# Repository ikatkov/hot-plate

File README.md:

# Hot plate for PCB rework and reflow

# Notes

## General

The heating is not uniform (enough?). The father points of the hotplate are ~5C colder than the center, where the ceramic heating element is located. Typically, one would expect it to even out, but due to the high temperature of operation (150C-200C), fringes lose heat at a higher rate. 

A typical PCB is made of FR4 glass-reinforced epoxy resin laminate, turns out it's a decent insulator. As the result, the top side of the PCB is ~25C colder than the hotplate surface. Perhaps lots of plated vias would transfer the heat better. Add this 25C if running the plate on manual control. Adjust reflow profile accordingly.

If FR4 start to smoke - it's way too hot or too hot for way too long. If that has happened, the FR4 substrate has likely expanded already. So it might have ruined your impedance-controlled traces. 

Reflow should take less than 5min from the cold PCB to the end, all three phases - preheat, soak, reflow.

One good practice is to use the hot plate as preheating only, set it to ~150C and then use the hot air solder station to activate and melt the solder paste.

Temperature variation ±5C does not matter. You want to heat, solder, and cool down as fast as possible.

Max rate of heating for this particular hotplate element is about +2C/sec, still air colling is -1C/sec.

You can place some container/insulation over the hot plate to reduce the heat loss, but it only raises the temperature by about +5C. On the other hand, you can blow over the PCB and instantly lower the temperature by a few degrees.

## Hardware

The temperature probe must be placed right on the heater element or as close as possible. Any significant time delay between temperature control and measurement will destabilize the control loop. 
The wrong way is to put a thermocouple probe on the plate's far side. It introduces about 15seconds of dead time. 
The right way is to shove it into the ceramic heater.

Watch out for the metal case shorting signal lines to the ground. Everything on the low-voltage side of the PCB must be insulated from the metal enclosure.

The thermocouple wire can be cut to a convenient length.

## Software

MAX6675 has a resolution of 0.25C and an accuracy of ±2C. It takes approx ~200ms to take a reading, i.e., the fastest possible control loop cycle is 4Hz.

A solid-state relay can turn off at every 1/2 cycle of the AC sinus wave. The maximum delay for 60 Hz AC power is 1/2 cycle or 8.33 ms.
Every 266.67ms or 32 half AC cycles, the algo measures the temperature, does PID computations, and decides on the PWM duty cycle for the next control cycle.

PWM cycle is 266.67ms, which we split into 2^5 intervals. Therefore we have 2^5 control bits.
PID output variable will range from 0 to 32;
Timer2 is set for interrupts at a 120Hz rate (because half-cycles)

The Max rate of heating for this particular hotplate element is about +2C/sec below 180C and ~1C above, still air colling is approx +1C/sec. So Arduino PID library is modified to half differential coefficient to accommodate this.

I had fun fine-tuning PID coefficients to get a fast response and avoid overshoot, but this temperature fidelity does not mater. 

# Fabrication

Assemble all these pieces together
* Heating plate, [like this]("hot-plate.png")
* IEC 320-C14 Receptacle, Male Blades, panel mount, this is the socket at the back
* SPDT AC 250V switch, this is the main power switch
* metal case with lot's of slots
* 3d printed enclosure for display pcb, [picture](display-board-case.png) , [STEP file](display-case.step)
* two pcbs, see below
* M3 screews, washers, stand-outs, kapton tape, 14AWG wire for mains, thermocouple wire, IDC ribbon, silicon antiskid pads

## Safety

### Electrical
Bond ground wire from mains to the metal case, as soon as it enters the enclosure. Wire both hot and neutral through the SPDT switch to the pcb connectors. Observe neutral/hot polarity on the pcb. The hotplate aluminum is bonded via M3 screw via standout to the metal case.

The main pcb (power board) has a MOV and a 2A fuse. MCU is on isolated supply.

### Thermal 

Powerboard pcb has 85C thermal fuse to protect AC-DC convertor, wires and other electornic components. The temperature gradient below the hot plate is quite significant. When the hot plate is at +200C, the tallest point of the PCB, and thus the closest point to the hot measures +45C, with +20C ambient.

Arduino PID firmware limits (software) hotplate max temperature to +230C, the heating plate has +260C thermostat inside. Firmware also limits heating to 30min max.

## Power board 

### BOM
| Refs | Qty | Component | Description |
| ----- | --- | ---- | ----------- |
| BZ1 | 1 | Buzzer | Buzzer, polarized |
| C1 | 1 | 220uF | Polarized capacitor, US symbol |
| D1 | 1 | LED | Light emitting diode |
| F1 | 1 | Temp Fuse 85C | Fuse |
| F2 | 1 | Fuse 2A | Fuse |
| J1 | 1 | LINE/LOAD | Any wire to board connector |
| J2 | 1 | DISPLAY | IDC ribbon connector |
| J3 | 1 | PROG | Panel mount connector |
| K1 | 1 | G3MB-202P | https://www.mouser.com/datasheet/2/307/g3mb_0609-1189645.pdf |
| Q1 | 1 | 2N2222A | Any NPN transistor, collector/base/emitter |
| R1, R2, R3, R4 | 4 | 10k | Resistor |
| R5, R6 | 2 | 1k | Resistor |
| RV1 | 1 | 10D391K | https://www.mouser.com/datasheet/2/54/mov10d-777448.pdf |
| U1 | 1 | HLK-PM01 | https://datasheet.lcsc.com/szlcsc/1909111105_HI-LINK-HLK-PM24_C399250.pdf |
| U2 | 1 | Arduino | Any AVR MCU with 32Kb+ of flash, 2Kb+ of RAM |
| U3 | 1 | MAX6675 | https://datasheets.maximintegrated.com/en/ds/MAX6675.pdf |

## Display board 

### BOM

| Refs | Qty | Component | Description |
| ----- | --- | ---- | ----------- |
| J1 | 1 | TO_PWR_BOARD | IDC ribbon connector |
| J2 | 1 | OLED DISPLAY | 0.91" OLED LCD Display Module SSD1306 IIC 128x32|
| SW1,SW2,SW3,SW4 | 1 | BUTTON_X | Momentary switch, button should be tall enough to stick out from the case |

[STEP file]("display-case.step")
.

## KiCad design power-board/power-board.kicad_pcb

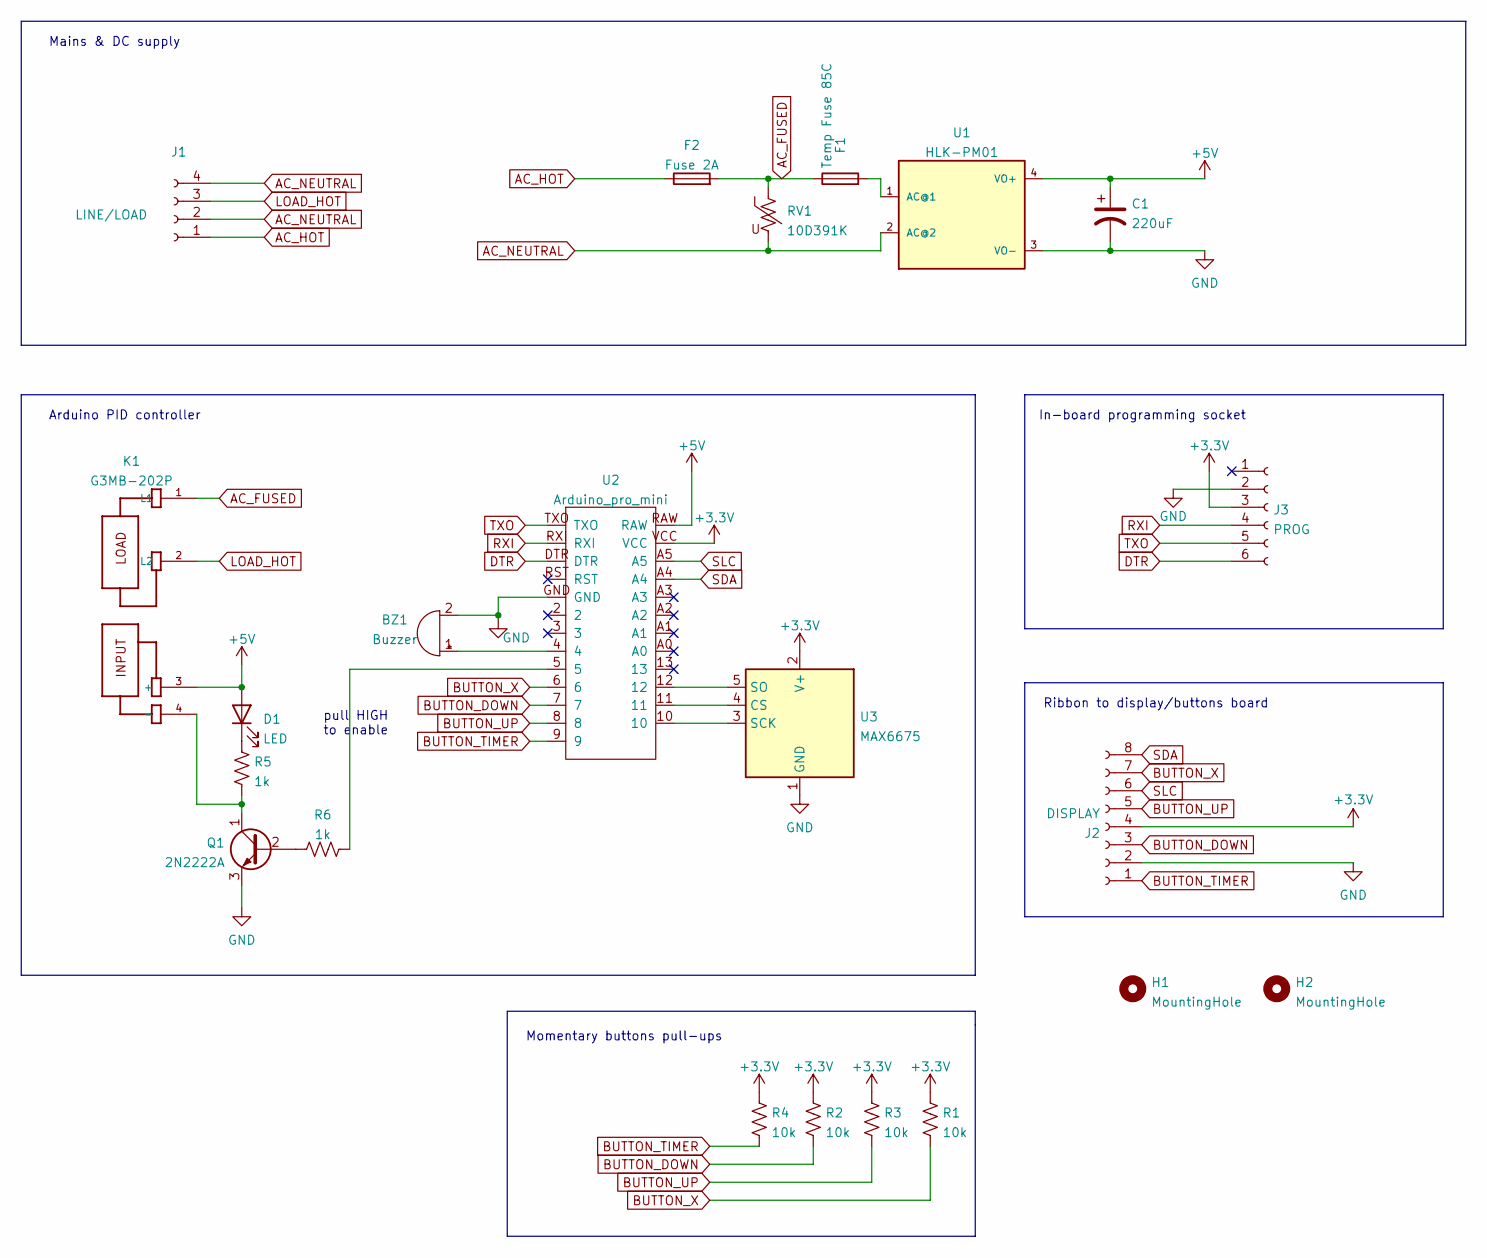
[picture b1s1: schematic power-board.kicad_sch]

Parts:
BZ1: Buzzer; Buzzer-GT-0905A
C1: 220uF; CP_Radial_D8.0mm_P5.00mm
D1: LED; LED_D5.0mm
F1: Temp Fuse 85C; R_Axial_DIN0414_L11.9mm_D4.5mm_P5.08mm_Vertical
F2: Fuse 2A; R_Axial_DIN0414_L11.9mm_D4.5mm_P5.08mm_Vertical
H1, H2: MountingHole; MountingHole_3.2mm_M3
J1: LINE/LOAD; WAGO_250-204_4_terminalblock
J2: DISPLAY; IDC-Header_2x04_P2.54mm_Vertical
J3: PROG; Connector_Mini-DIN_Female_6Pin_2rows
K1: G3MB-202P; RELAY_G3MB-202P
Q1: 2N2222A; TO-92L_Wide
R1, R2, R3, R4: 10k; R_Axial_DIN0204_L3.6mm_D1.6mm_P7.62mm_Horizontal
R5, R6: 1k; R_Axial_DIN0204_L3.6mm_D1.6mm_P7.62mm_Horizontal
RV1: 10D391K; RV_Disc_D12mm_W3.9mm_P7.5mm
U1: HLK-PM01
U2: Arduino_pro_mini; ARDUINO_PRO_MINI
U3: MAX6675; Thermocouple module

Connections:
+3V3: J2.4, J3.3, R1.1, R2.1, R3.1, R4.1, U2.VCC, U3.2 (V+)
+5V: C1.1, D1.2 (A), K1.3 (+), U1.4 (VO+), U2.RAW
AC_FUSED: F1.1, F2.2, K1.1 (L1), RV1.1
AC_HOT: F2.1, J1.1
AC_NEUTRAL: J1.2, J1.4, RV1.2, U1.2 (AC@2)
BUTTON_DOWN: J2.3, R2.2, U2.7
BUTTON_TIMER: J2.1, R4.2, U2.9
BUTTON_UP: J2.5, R3.2, U2.8
BUTTON_X: J2.7, R1.2, U2.6
DTR: J3.6, U2.DTR
GND: BZ1.2 (+), C1.2, J2.2, J3.2, Q1.3 (E), U1.3 (VO-), U2.GND, U3.1 (GND)
LOAD_HOT: J1.3, K1.2 (L2)
unnamed: BZ1.1 (-), U2.4
unnamed: D1.1 (K), R5.1
unnamed: F1.2, U1.1 (AC@1)
unnamed: K1.4 (-), Q1.1 (C), R5.2
unnamed: Q1.2 (B), R6.1
unnamed: R6.2, U2.5
unnamed: U2.10, U3.3 (SCK)
unnamed: U2.11, U3.4 (CS)
unnamed: U2.12, U3.5 (SO)
RXI: J3.4, U2.RXI
SDA: J2.8, U2.A4
SLC: J2.6, U2.A5
TXO: J3.5, U2.TXO

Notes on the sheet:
In-board programming socket
Ribbon to display/buttons board
Arduino PID controller
pull HIGH to enable
Momentary buttons pull-ups
Mains & DC supply

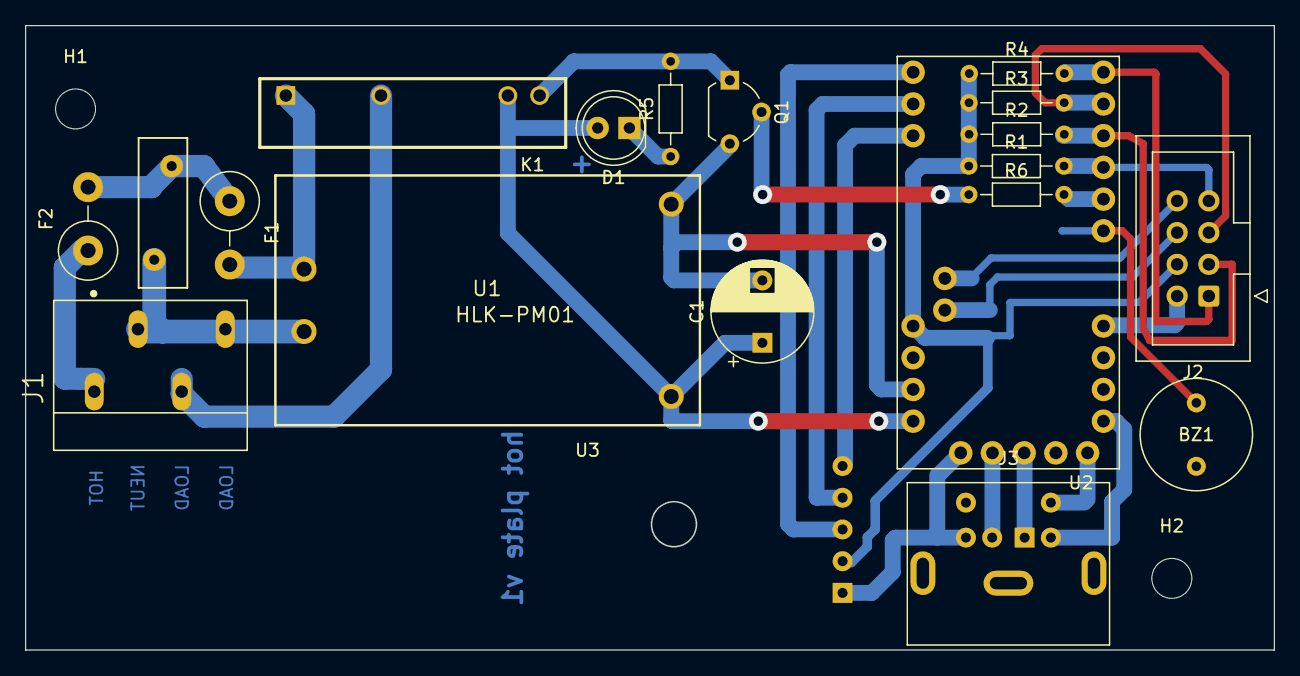
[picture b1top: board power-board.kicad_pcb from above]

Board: 2 copper layers, 100.0 x 50.0 mm, 22 parts (0 on the bottom side), 25 nets.

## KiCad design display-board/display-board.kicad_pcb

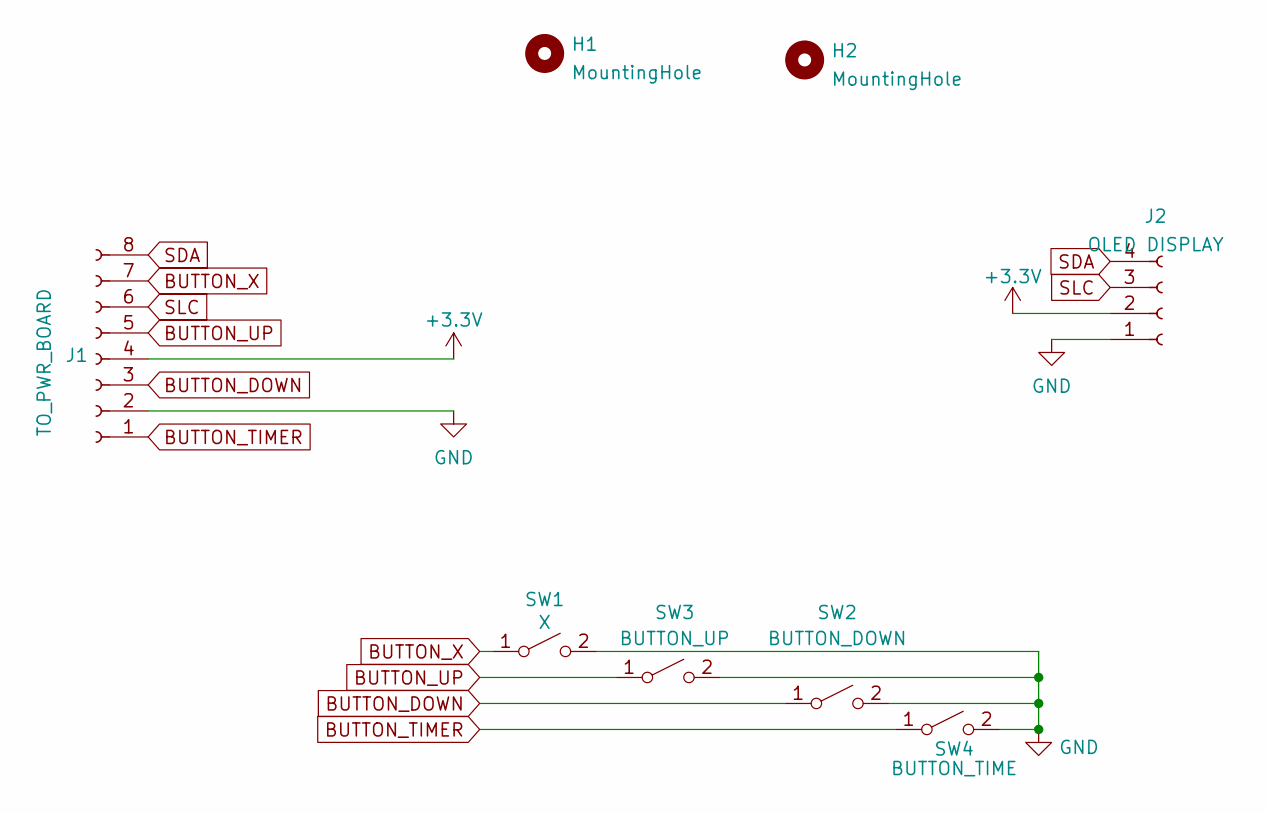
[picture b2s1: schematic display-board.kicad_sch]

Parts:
H1, H2: MountingHole; MountingHole_3.2mm_M3
J1: TO_PWR_BOARD; IDC-Header_2x04_P2.54mm_Vertical
J2: OLED DISPLAY; SSD1306-0.91-OLED-4pin-128x32
SW1: X; SW_PUSH_6mm_H4.3mm
SW2: BUTTON_DOWN; SW_PUSH_6mm_H4.3mm
SW3: BUTTON_UP; SW_PUSH_6mm_H4.3mm
SW4: BUTTON_TIME; SW_PUSH_6mm_H4.3mm

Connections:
+3V3: J1.4, J2.2
BUTTON_DOWN: J1.3, SW2.1 (A)
BUTTON_TIMER: J1.1, SW4.1 (A)
BUTTON_UP: J1.5, SW3.1 (A)
BUTTON_X: J1.7, SW1.1 (A)
GND: J1.2, J2.1, SW1.2 (B), SW2.2 (B), SW3.2 (B), SW4.2 (B)
SDA: J1.8, J2.4
SLC: J1.6, J2.3

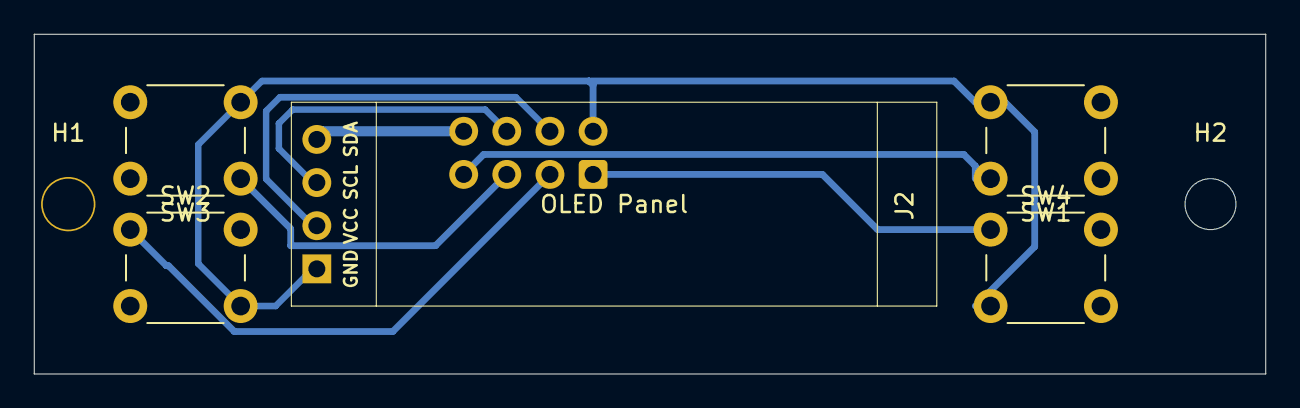
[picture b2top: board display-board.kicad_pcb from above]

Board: 4 copper layers, 72.5 x 20.0 mm, 8 parts (1 on the bottom side), 8 nets.

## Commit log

2022-04-04 documentation
2022-04-04 license
2022-04-04 typos fixed
2022-04-04 typos
